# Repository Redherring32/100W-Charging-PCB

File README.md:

# 100W-Charging-PCB
100W USB C PD Lithium Ion charging PCB based on the TPS25750D and BQ25713

This PCB is spec'd for 20V 5A USB C PD charging of a 1S configuration of Lithium Ion cells, it is suitable for dropping into a variety of battery powered projects that may be a bit more power hungry or where faster charging may be desired.
Within this repository you can find everything to build this PCB, as well as source design files for it should you need to repurpose it for a different form factor or design.

# PCB SPECS:
* 4 layers
* 38.5x38.5mm
* filled vias (VIPPO) is recommended for assembly reasons due to via in pad

## LICENSE:
Licensed under
the TAPR Open hardware license (www.tapr.org/OHL)

©Redherring32 2024

## DISCLAIMER:

Lithium Ion Batteries are DANGEROUS, they should not be handled if you do not know what you are doing.
I offer this with no warranty, express or implied, and I am NOT responsible for anything that may happen as a result of misuse of this PCB.
You have been warned.

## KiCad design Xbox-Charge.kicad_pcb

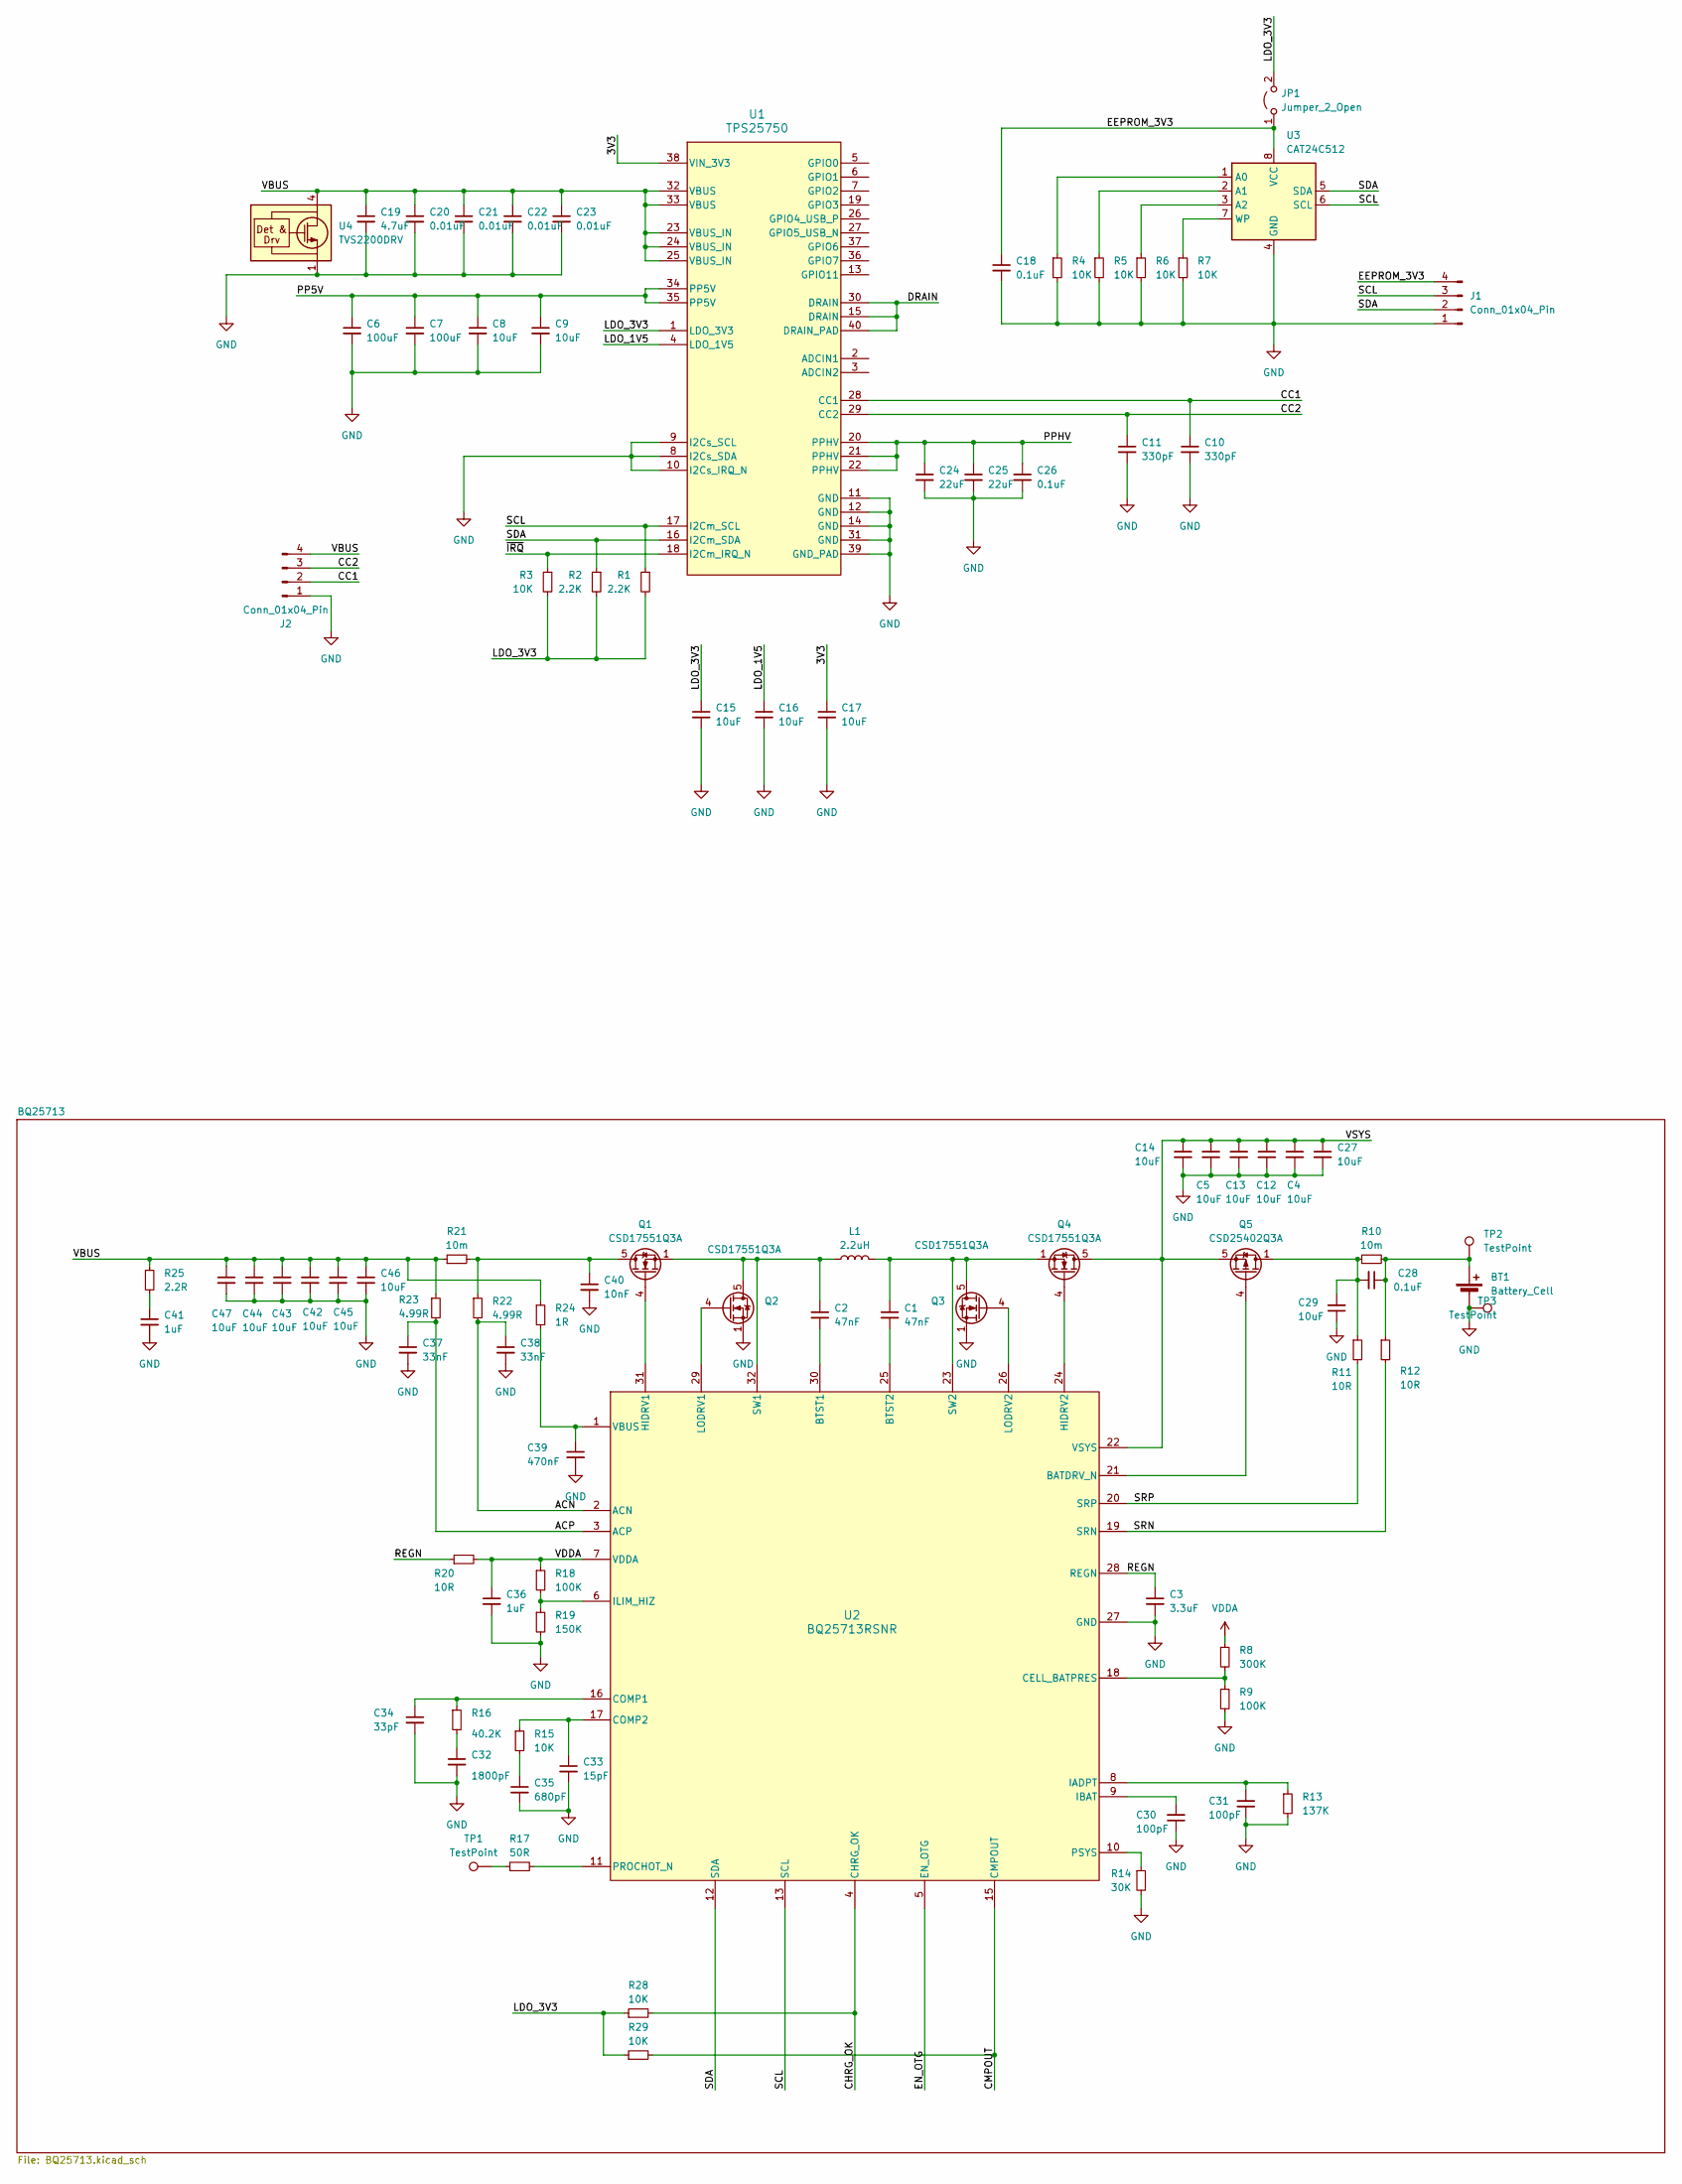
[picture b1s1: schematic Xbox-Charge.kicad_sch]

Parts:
BT1: Battery_Cell
C1, C2: 47nF; C_0603_1608Metric
C3: 3.3uF; C_0603_1608Metric
C4, C5, C12, C13, C14, C27, C42, C43, C44, C45, C46, C47: 10uF; C_0805_2012Metric
C6, C7: 100uF; C_1210_3225Metric
C8, C9, C29: 10uF; C_0603_1608Metric
C10, C11: 330pF; C_0201_0603Metric
C15, C16, C17: 10uF; C_0402_1005Metric
C18, C26: 0.1uF; C_0402_1005Metric
C19: 4.7uF; C_0805_2012Metric
C20, C21, C22, C23: 0.01uF; C_0402_1005Metric
C24, C25: 22uF; C_0805_2012Metric
C28: 0.1uF; C_0603_1608Metric
C30, C31: 100pF; C_0603_1608Metric
C32: 1800pF; C_0402_1005Metric
C33: 15pF; C_0402_1005Metric
C34: 33pF; C_0402_1005Metric
C35: 680pF; C_0402_1005Metric
C36: 1uF; C_0402_1005Metric
C37, C38: 33nF; C_0603_1608Metric
C39: 470nF; C_0805_2012Metric
C40: 10nF; C_0402_1005Metric
C41: 1uF
J1: Conn_01x04_Pin; PROG
J2: Conn_01x04_Pin; VBUS PADS
JP1: Jumper_2_Open; SolderJumper-2_P1.3mm_Open_RoundedPad1.0x1.5mm
L1: 2.2uH; L_Chilisin_BMRx00060630
Q1, Q2, Q3, Q4: CSD17551Q3A; VSON-8_3.3x3.3mm_P0.65mm_NexFET
Q5: CSD25402Q3A; VSON-8_3.3x3.3mm_P0.65mm_NexFET
R1, R2: 2.2K; R_0402_1005Metric
R3, R4, R5, R6, R7, R15, R28, R29: 10K; R_0402_1005Metric
R8: 300K; R_0402_1005Metric
R9, R18: 100K; R_0402_1005Metric
R10, R21: 10m; R_1206_3216Metric
R11, R12: 10R; R_0603_1608Metric
R13: 137K; R_0603_1608Metric
R14: 30K; R_0603_1608Metric
R16: 40.2K; R_0402_1005Metric
R17: 50R
R19: 150K; R_0402_1005Metric
R20: 10R; R_0402_1005Metric
R22, R23: 4.99R; R_0603_1608Metric
R24: 1R; R_0805_2012Metric
R25: 2.2R
TP1: TestPoint
TP2, TP3: TestPoint; TestPoint_Pad_3.0x3.0mm
U1: TPS25750; TPS25750D
U2: BQ25713RSNR; Texas_RSN_WQFN-32-1EP_4x4mm_P0.4mm_EP2.8x2.8mm
U3: CAT24C512; SOIC-8_3.9x4.9mm_P1.27mm
U4: TVS2200DRV; WSON-6-1EP_2x2mm_P0.65mm_EP1x1.6mm

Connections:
/3V3: C17.1, U1.38 (VIN_3V3)
/ACN: C38.1, R22.2, U2.2 (ACN)
/ACP: C37.1, R23.2, U2.3 (ACP)
/CC1: C10.1, J2.2, U1.28 (CC1)
/CC2: C11.1, J2.3, U1.29 (CC2)
/CHRG_OK: R28.2, U2.4 (CHRG_OK)
/CMPOUT: R29.2, U2.15 (CMPOUT)
/DRAIN: U1.15 (DRAIN), U1.30 (DRAIN), U1.40 (DRAIN_PAD)
/EEPROM_3V3: C18.1, J1.4, JP1.1 (A), U3.8 (VCC)
/EN_OTG: U2.5 (EN_OTG)
/LDO_1V5: C16.1, U1.4 (LDO_1V5)
/LDO_3V3: C15.1, JP1.2 (B), R1.2, R2.2, R3.2, R28.1, R29.1, U1.1 (LDO_3V3)
/PP5V: C6.1, C7.1, C8.1, C9.1, U1.34 (PP5V), U1.35 (PP5V)
/PPHV: C24.1, C25.1, C26.1, U1.20 (PPHV), U1.21 (PPHV), U1.22 (PPHV)
/REGN: C3.1, R20.1, U2.28 (REGN)
/SCL: J1.3, R1.1, U1.17 (I2Cm_SCL), U2.13 (SCL), U3.6 (SCL)
/SDA: J1.2, R2.1, U1.16 (I2Cm_SDA), U2.12 (SDA), U3.5 (SDA)
/SRN: R12.2, U2.19 (SRN)
/SRP: R11.2, U2.20 (SRP)
/VBUS: C19.1, C20.1, C21.1, C22.1, C23.1, C42.1, C43.1, C44.1, C45.1, C46.1, C47.1, J2.4, R21.1, R23.1, R24.1, R25.1, U1.23 (VBUS_IN), U1.24 (VBUS_IN), U1.25 (VBUS_IN), U1.32 (VBUS), U1.33 (VBUS), U4.4 (IN), U4.5 (IN), U4.6 (IN)
/VSYS: C4.1, C5.1, C12.1, C13.1, C14.1, C27.1, Q4.5 (D), Q5.5 (S), U2.22 (VSYS)
/~IRQ: R3.1, U1.18 (I2Cm_IRQ_N)
GND: BT1.2 (-), C3.2, C4.2, C5.2, C6.2, C7.2, C8.2, C9.2, C10.2, C11.2, C12.2, C13.2, C14.2, C15.2, C16.2, C17.2, C18.2, C19.2, C20.2, C21.2, C22.2, C23.2, C24.2, C25.2, C26.2, C27.2, C29.1, C30.1, C31.2, C32.2, C33.2, C34.2, C35.2, C36.2, C37.2, C38.2, C39.2, C40.2, C41.2, C42.2, C43.2, C44.2, C45.2, C46.2, C47.2, J1.1, J2.1, Q2.1 (S), Q2.2 (S), Q2.3 (S), Q3.1 (S), Q3.2 (S), Q3.3 (S), R4.2, R5.2, R6.2, R7.2, R9.2, R13.2, R14.2, R19.2, TP3.1, U1.8 (I2Cs_SDA), U1.9 (I2Cs_SCL), U1.10 (I2Cs_IRQ_N), U1.11 (GND), U1.12 (GND), U1.14 (GND), U1.31 (GND), U1.39 (GND_PAD), U2.27 (GND), U2.33 (PAD), U3.4 (GND), U4.1 (GND), U4.2 (GND), U4.3 (GND), U4.7 (GND)
unnamed: BT1.1 (+), C28.1, R10.2, R12.1, TP2.1
unnamed: C28.2, C29.2, Q5.1 (D), Q5.2 (D), Q5.3 (D), R10.1, R11.1
unnamed: C32.1, R16.2
unnamed: C35.1, R15.2
unnamed: C41.1, R25.2
unnamed: C40.1, Q1.5 (D), R21.2, R22.1
unnamed: Q1.4 (G), U2.31 (HIDRV1)
unnamed: C2.1, L1.1, Q1.1 (S), Q1.2 (S), Q1.3 (S), Q2.5 (D), U2.32 (SW1)
unnamed: Q2.4 (G), U2.29 (LODRV1)
unnamed: C1.1, L1.2, Q3.5 (D), Q4.1 (S), Q4.2 (S), Q4.3 (S), U2.23 (SW2)
unnamed: Q3.4 (G), U2.26 (LODRV2)
unnamed: Q4.4 (G), U2.24 (HIDRV2)
unnamed: Q5.4 (G), U2.21 (BATDRV_N)
unnamed: R17.1, TP1.1
unnamed: C2.2, U2.30 (BTST1)
unnamed: C1.2, U2.25 (BTST2)
unnamed: R8.2, R9.1, U2.18 (CELL_BATPRES)
unnamed: C34.1, R16.1, U2.16 (COMP1)
unnamed: C33.1, R15.1, U2.17 (COMP2)
unnamed: C31.1, R13.1, U2.8 (IADPT)
unnamed: C30.2, U2.9 (IBAT)
unnamed: R18.2, R19.1, U2.6 (ILIM_HIZ)
unnamed: R17.2, U2.11 (PROCHOT_N)
unnamed: R14.1, U2.10 (PSYS)
unnamed: C39.1, R24.2, U2.1 (VBUS)
unnamed: R4.1, U3.1 (A0)
unnamed: R5.1, U3.2 (A1)
unnamed: R6.1, U3.3 (A2)
unnamed: R7.1, U3.7 (WP)
VDDA: C36.1, R8.1, R18.1, R20.2, U2.7 (VDDA)

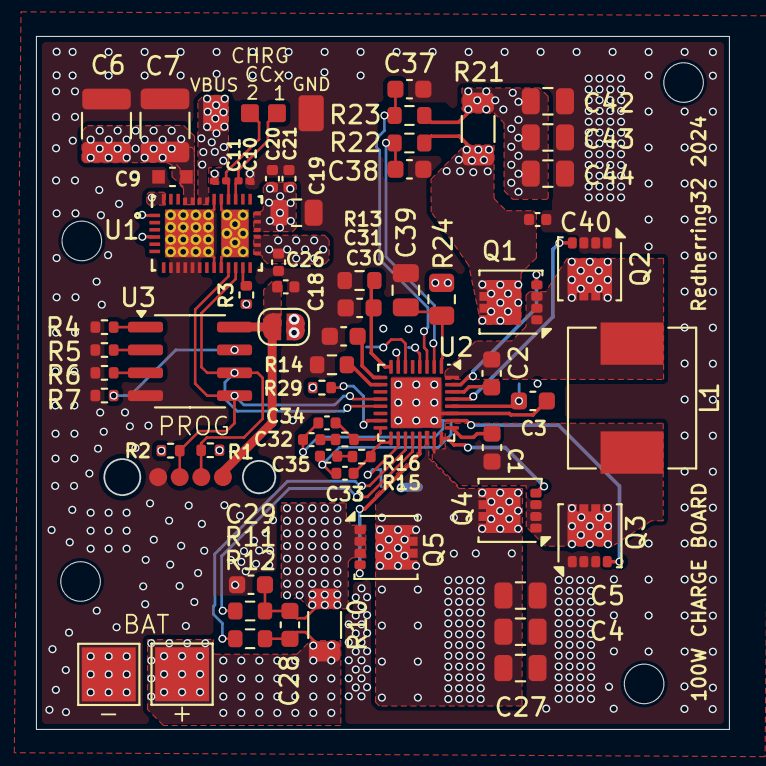
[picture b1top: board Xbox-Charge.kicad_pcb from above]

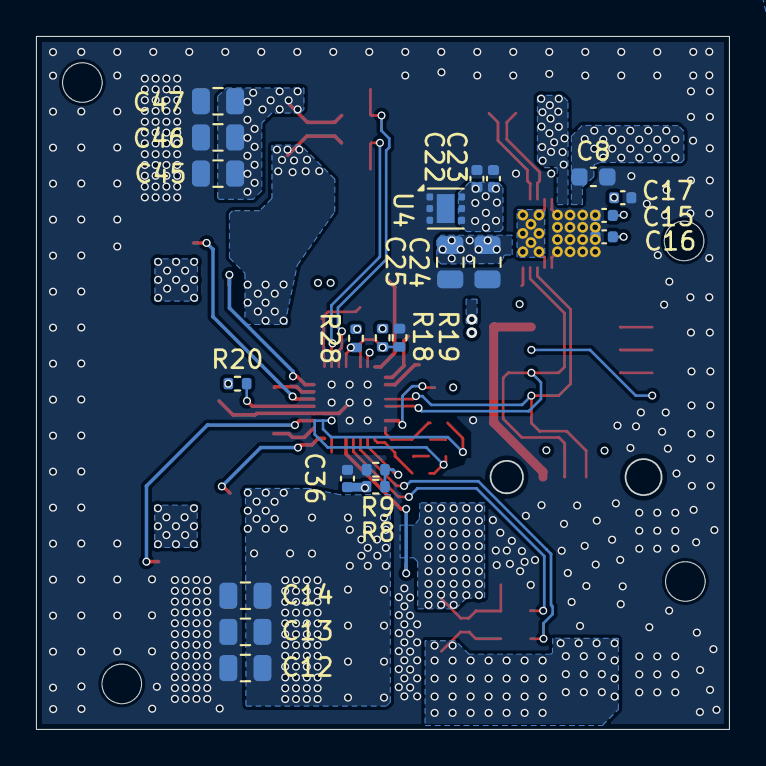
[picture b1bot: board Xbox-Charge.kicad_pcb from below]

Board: 13 copper layers, 38.4 x 38.5 mm, 86 parts (22 on the bottom side), 49 nets.

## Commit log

2024-08-13 Add files and LICENSE
2024-08-17 Update README.md
    Add PCB specs and fix typos.
2024-08-17 Cleaned up schematic and split BQ25713 circuit off to a second sheet
